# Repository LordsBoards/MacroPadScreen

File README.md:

# A macropad + numpad to keep close by on your desk.
Uses the https://www.adafruit.com/product/2158 many-segment display for cyberpunk aesthetics

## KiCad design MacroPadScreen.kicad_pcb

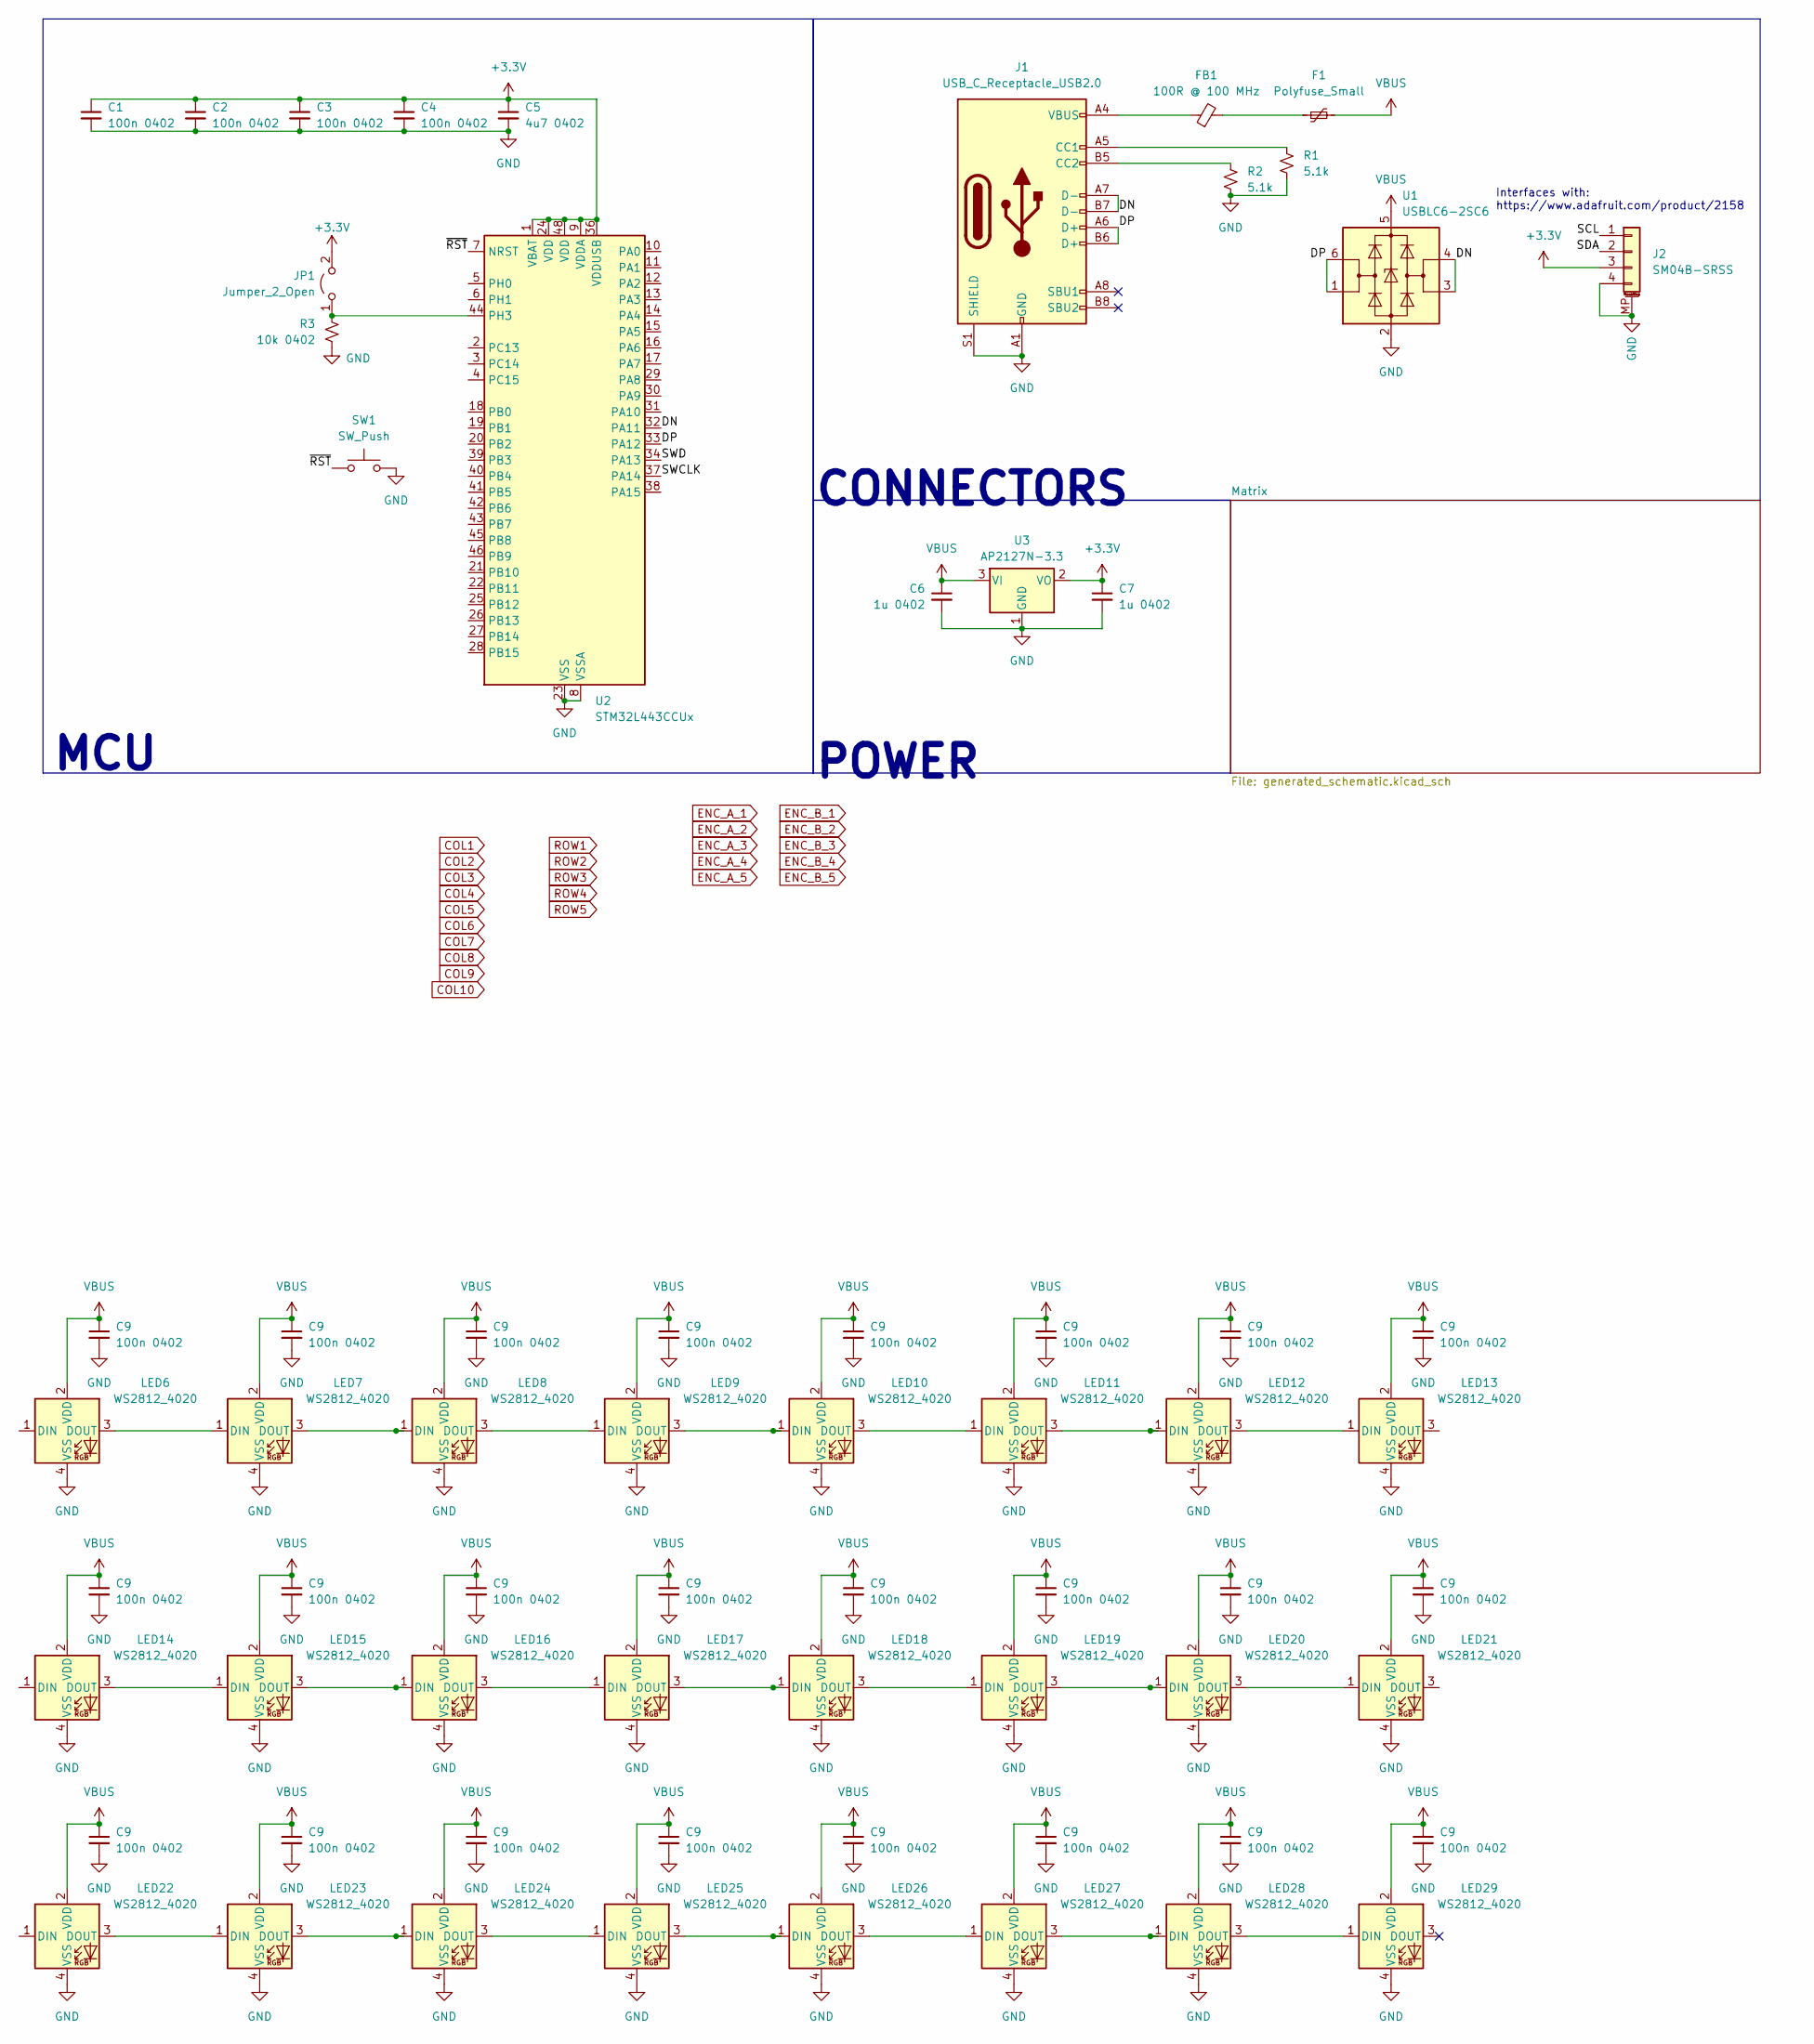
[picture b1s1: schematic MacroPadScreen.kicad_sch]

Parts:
C1, C2, C3, C4, C9: 100n 0402; C_0402_1005Metric
C5: 4u7 0402; C_0402_1005Metric
C6, C7: 1u 0402; C_0402_1005Metric
F1: Polyfuse_Small
FB1: 100R @ 100 MHz
J1: USB_C_Receptacle_USB2.0; USB_C_Receptacle_HRO_TYPE-C-31-M-12
J2: SM04B-SRSS; JST_SH_SM04B-SRSS-TB_1x04-1MP_P1.00mm_Horizontal; Manufacturer Part Number SM04B-SRSS-TB; LCSC Part Number C160404
JP1: Jumper_2_Open; PinHeader_1x02_P1.27mm_Vertical
LED6, LED7, LED8, LED9, LED10, LED11, LED12, LED13, LED14, LED15, LED16, LED17, LED18, LED19, LED20, LED21, LED22, LED23, LED24, LED25, LED26, LED27, LED28, LED29: WS2812_4020; LED_WS2812_4020
R1, R2: 5.1k; R_0402_1005Metric
R3: 10k 0402; R_0402_1005Metric; LCSC C60490
SW1: SW_Push; SW_Push_1P1T_XKB_TS-1187A
U1: USBLC6-2SC6; SOT-23-6
U2: STM32L443CCUx; QFN-48-1EP_7x7mm_P0.5mm_EP5.6x5.6mm
U3: AP2127N-3.3; SOT-23

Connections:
+3.3V: C1.1, C2.1, C3.1, C4.1, C5.1, C7.1, J2.3, JP1.2 (B), U2.1 (VBAT), U2.9 (VDDA), U2.24 (VDD), U2.36 (VDDUSB), U2.48 (VDD), U3.2 (VO); also elsewhere on the board
/DN: J1.A7 (D-), J1.B7 (D-), U1.3 (I/O2), U1.4 (I/O2), U2.32 (PA11)
/DP: J1.A6 (D+), J1.B6 (D+), U1.1 (I/O1), U1.6 (I/O1), U2.33 (PA12)
/SCL: J2.1
/SDA: J2.2
/SWCLK: U2.37 (PA14)
/SWD: U2.34 (PA13)
/~RST: SW1.1, U2.7 (NRST)
GND: C1.2, C2.2, C3.2, C4.2, C5.2, C6.2, C7.2, C9.2, J1.A1 (GND), J1.A12 (GND), J1.B1 (GND), J1.B12 (GND), J1.S1 (SHIELD), J2.4, J2.MP (MountPin), LED6.4 (VSS), LED7.4 (VSS), LED8.4 (VSS), LED9.4 (VSS), LED10.4 (VSS), LED11.4 (VSS), LED12.4 (VSS), LED13.4 (VSS), LED14.4 (VSS), LED15.4 (VSS), LED16.4 (VSS), LED17.4 (VSS), LED18.4 (VSS), LED19.4 (VSS), LED20.4 (VSS), LED21.4 (VSS), LED22.4 (VSS), LED23.4 (VSS), LED24.4 (VSS), LED25.4 (VSS), LED26.4 (VSS), LED27.4 (VSS), LED28.4 (VSS), LED29.4 (VSS), R1.2, R2.2, R3.2, SW1.2, U1.2 (GND), U2.8 (VSSA), U2.23 (VSS), U2.35 (VSS), U2.47 (VSS), U2.49 (VSS), U3.1 (GND); also elsewhere on the board
unnamed: F1.1, FB1.2
unnamed: FB1.1, J1.A4 (VBUS), J1.A9 (VBUS), J1.B4 (VBUS), J1.B9 (VBUS)
unnamed: J1.A5 (CC1), R1.1
unnamed: J1.B5 (CC2), R2.1
unnamed: JP1.1 (A), R3.1, U2.44 (PH3)
unnamed: LED6.3 (DOUT), LED7.1 (DIN)
unnamed: LED7.3 (DOUT), LED8.1 (DIN)
unnamed: LED8.3 (DOUT), LED9.1 (DIN)
unnamed: LED9.3 (DOUT), LED10.1 (DIN)
unnamed: LED10.3 (DOUT), LED11.1 (DIN)
unnamed: LED11.3 (DOUT), LED12.1 (DIN)
unnamed: LED12.3 (DOUT), LED13.1 (DIN)
unnamed: LED14.3 (DOUT), LED15.1 (DIN)
unnamed: LED15.3 (DOUT), LED16.1 (DIN)
unnamed: LED16.3 (DOUT), LED17.1 (DIN)
unnamed: LED17.3 (DOUT), LED18.1 (DIN)
unnamed: LED18.3 (DOUT), LED19.1 (DIN)
unnamed: LED19.3 (DOUT), LED20.1 (DIN)
unnamed: LED20.3 (DOUT), LED21.1 (DIN)
unnamed: LED22.3 (DOUT), LED23.1 (DIN)
unnamed: LED23.3 (DOUT), LED24.1 (DIN)
unnamed: LED24.3 (DOUT), LED25.1 (DIN)
unnamed: LED25.3 (DOUT), LED26.1 (DIN)
unnamed: LED26.3 (DOUT), LED27.1 (DIN)
unnamed: LED27.3 (DOUT), LED28.1 (DIN)
unnamed: LED28.3 (DOUT), LED29.1 (DIN)
VBUS: C6.1, C9.1, LED6.2 (VDD), LED7.2 (VDD), LED8.2 (VDD), LED9.2 (VDD), LED10.2 (VDD), LED11.2 (VDD), LED12.2 (VDD), LED13.2 (VDD), LED14.2 (VDD), LED15.2 (VDD), LED16.2 (VDD), LED17.2 (VDD), LED18.2 (VDD), LED19.2 (VDD), LED20.2 (VDD), LED21.2 (VDD), LED22.2 (VDD), LED23.2 (VDD), LED24.2 (VDD), LED25.2 (VDD), LED26.2 (VDD), LED27.2 (VDD), LED28.2 (VDD), LED29.2 (VDD), U1.5 (VBUS), U3.3 (VI); also elsewhere on the board

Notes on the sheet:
POWER
Interfaces with: https://www.adafruit.com/product/2158
MCU
CONNECTORS

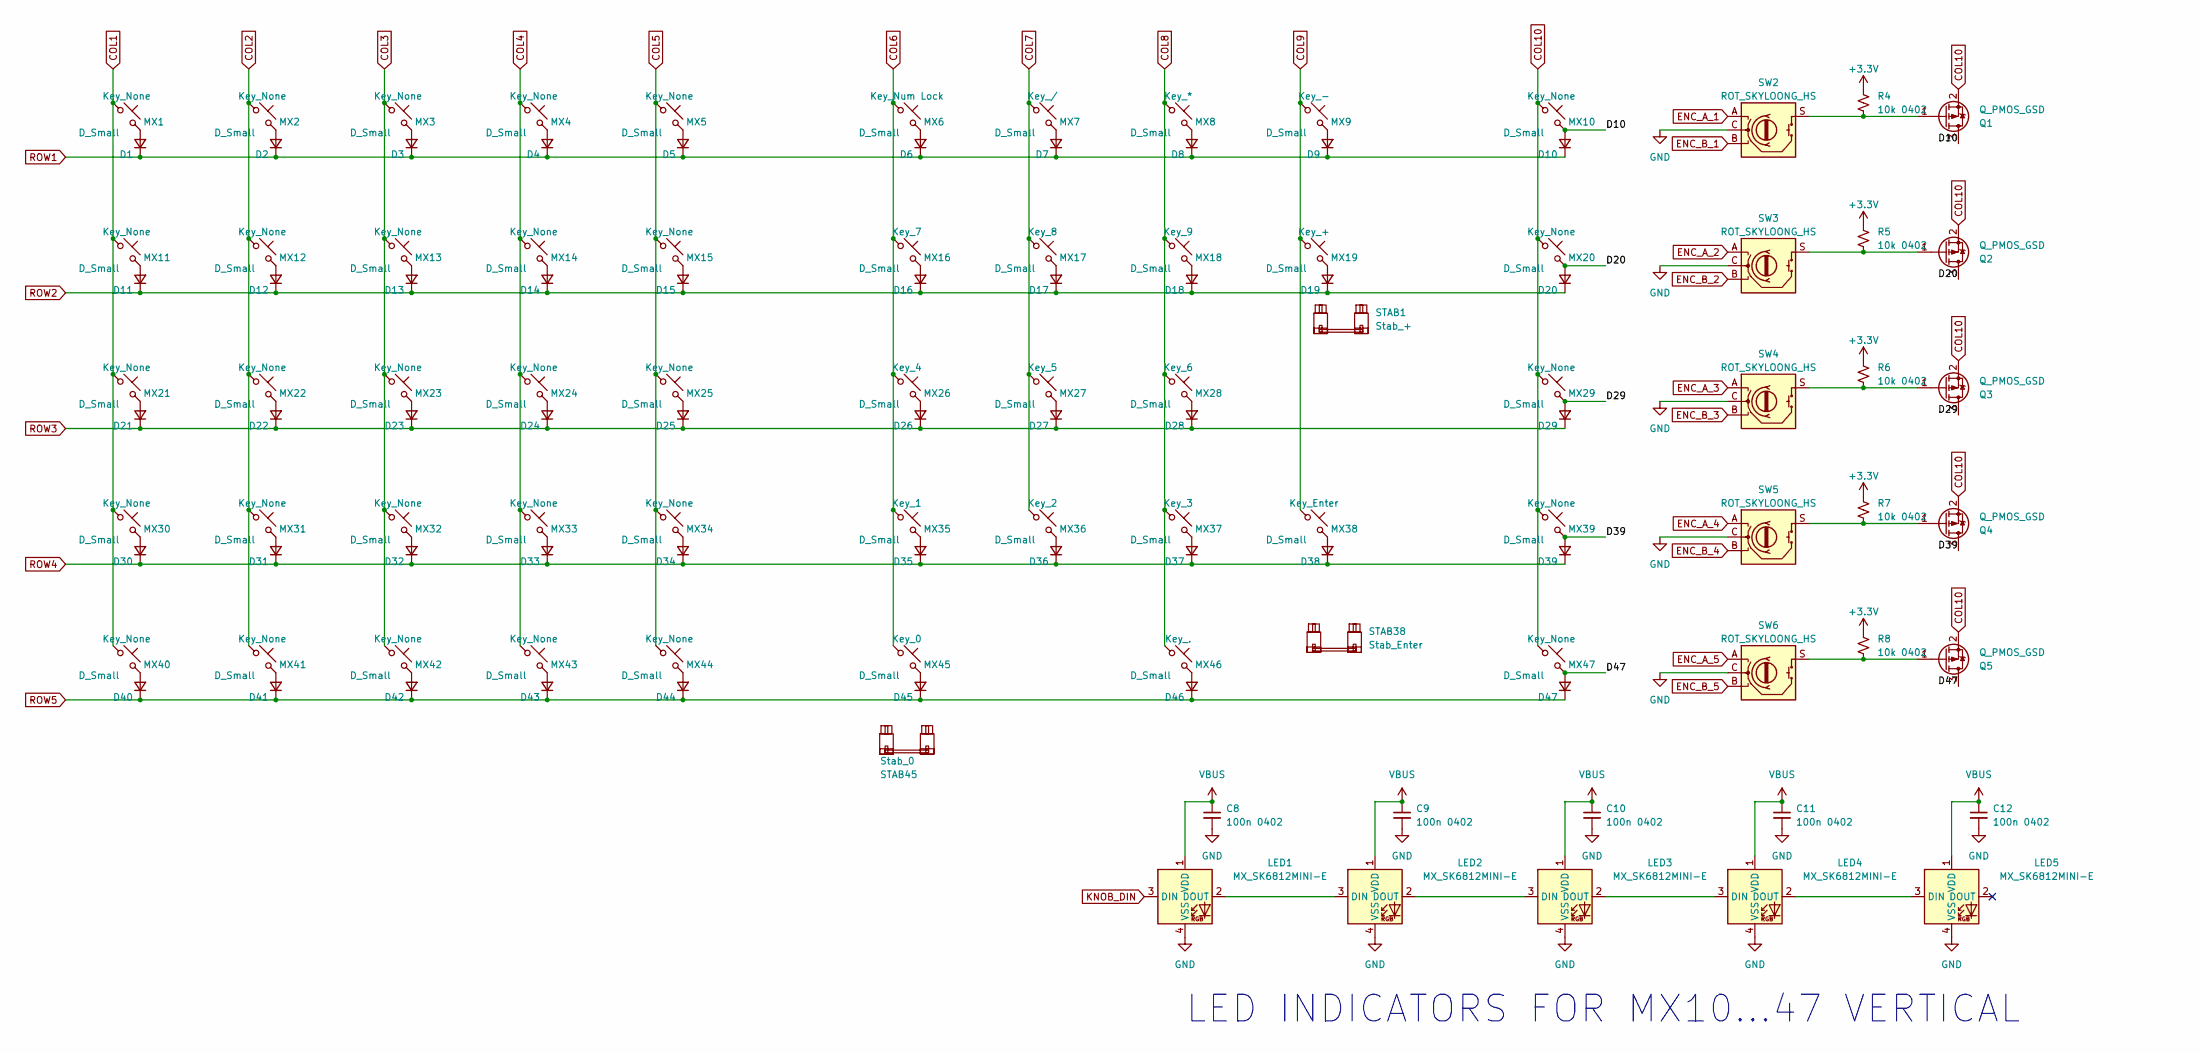
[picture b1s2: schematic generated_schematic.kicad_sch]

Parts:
C8, C9, C10, C11, C12: 100n 0402; C_0402_1005Metric
D1, D2, D3, D4, D5, D6, D7, D8, D9, D10, D11, D12, D13, D14, D15, D16, D17, D18, D19, D20, D21, D22, D23, D24, D25, D26, D27, D28, D29, D30, D31, D32, D33, D34, D35, D36, D37, D38, D39, D40, D41, D42, D43, D44, D45, D46, D47: D_Small; D_SOD-123
LED1, LED2, LED3, LED4, LED5: MX_SK6812MINI-E; LED_MX_6028R
MX1, MX2, MX3, MX4, MX5, MX10, MX11, MX12, MX13, MX14, MX15, MX20, MX21, MX22, MX23, MX24, MX25, MX29, MX30, MX31, MX32, MX33, MX34, MX39, MX40, MX41, MX42, MX43, MX44, MX47: Key_None; SW_MX_HS_S_1u
MX6: Key_Num Lock; SW_MX_HS_S_1u
MX7: Key_/; SW_MX_HS_S_1u
MX8: Key_*; SW_MX_HS_S_1u
MX9: Key_-; SW_MX_HS_S_1u
MX16: Key_7; SW_MX_HS_S_1u
MX17: Key_8; SW_MX_HS_S_1u
MX18: Key_9; SW_MX_HS_S_1u
MX19: Key_+; SW_MX_HS_S_1u
MX26: Key_4; SW_MX_HS_S_1u
MX27: Key_5; SW_MX_HS_S_1u
MX28: Key_6; SW_MX_HS_S_1u
MX35: Key_1; SW_MX_HS_S_1u
MX36: Key_2; SW_MX_HS_S_1u
MX37: Key_3; SW_MX_HS_S_1u
MX38: Key_Enter; SW_MX_HS_S_1u
MX45: Key_0; SW_MX_HS_S_1u
MX46: Key_.; SW_MX_HS_S_1u
Q1, Q2, Q3, Q4, Q5: Q_PMOS_GSD; SOT-23
R4, R5, R6, R7, R8: 10k 0402; R_0402_1005Metric
STAB1: Stab_+; STAB_MX_P_2u
STAB38: Stab_Enter; STAB_MX_P_2u
STAB45: Stab_0; STAB_MX_P_2u
SW2, SW3, SW4, SW5, SW6: ROT_SKYLOONG_HS; ROT_SKYLOONG_HS-Switch

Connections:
+3.3V: R4.1, R5.1, R6.1, R7.1, R8.1; also elsewhere on the board
/Matrix/D10: D10.2 (A), MX10.2, Q1.3 (D)
/Matrix/D20: D20.2 (A), MX20.2, Q2.3 (D)
/Matrix/D29: D29.2 (A), MX29.2, Q3.3 (D)
/Matrix/D39: D39.2 (A), MX39.2, Q4.3 (D)
/Matrix/D47: D47.2 (A), MX47.2, Q5.3 (D)
COL1: MX1.1, MX11.1, MX21.1, MX30.1, MX40.1
COL2: MX2.1, MX12.1, MX22.1, MX31.1, MX41.1
COL3: MX3.1, MX13.1, MX23.1, MX32.1, MX42.1
COL4: MX4.1, MX14.1, MX24.1, MX33.1, MX43.1
COL5: MX5.1, MX15.1, MX25.1, MX34.1, MX44.1
COL6: MX6.1, MX16.1, MX26.1, MX35.1, MX45.1
COL7: MX7.1, MX17.1, MX27.1, MX36.1
COL8: MX8.1, MX18.1, MX28.1, MX37.1, MX46.1
COL9: MX9.1, MX19.1, MX38.1
COL10: MX10.1, MX20.1, MX29.1, MX39.1, MX47.1, Q1.2 (S), Q2.2 (S), Q3.2 (S), Q4.2 (S), Q5.2 (S)
ENC_A_1: SW2.A
ENC_A_2: SW3.A
ENC_A_3: SW4.A
ENC_A_4: SW5.A
ENC_A_5: SW6.A
ENC_B_1: SW2.B
ENC_B_2: SW3.B
ENC_B_3: SW4.B
ENC_B_4: SW5.B
ENC_B_5: SW6.B
GND: C8.2, C9.2, C10.2, C11.2, C12.2, LED1.4 (VSS), LED2.4 (VSS), LED3.4 (VSS), LED4.4 (VSS), LED5.4 (VSS), SW2.C, SW3.C, SW4.C, SW5.C, SW6.C; also elsewhere on the board
KNOB_DIN: LED1.3 (DIN)
unnamed: D1.2 (A), MX1.2
unnamed: D2.2 (A), MX2.2
unnamed: D3.2 (A), MX3.2
unnamed: D4.2 (A), MX4.2
unnamed: D5.2 (A), MX5.2
unnamed: D6.2 (A), MX6.2
unnamed: D7.2 (A), MX7.2
unnamed: D8.2 (A), MX8.2
unnamed: D9.2 (A), MX9.2
unnamed: D11.2 (A), MX11.2
unnamed: D12.2 (A), MX12.2
unnamed: D13.2 (A), MX13.2
unnamed: D14.2 (A), MX14.2
unnamed: D15.2 (A), MX15.2
unnamed: D16.2 (A), MX16.2
unnamed: D17.2 (A), MX17.2
unnamed: D18.2 (A), MX18.2
unnamed: D19.2 (A), MX19.2
unnamed: D21.2 (A), MX21.2
unnamed: D22.2 (A), MX22.2
unnamed: D23.2 (A), MX23.2
unnamed: D24.2 (A), MX24.2
unnamed: D25.2 (A), MX25.2
unnamed: D26.2 (A), MX26.2
unnamed: D27.2 (A), MX27.2
unnamed: D28.2 (A), MX28.2
unnamed: D30.2 (A), MX30.2
unnamed: D31.2 (A), MX31.2
unnamed: D32.2 (A), MX32.2
unnamed: D33.2 (A), MX33.2
unnamed: D34.2 (A), MX34.2
unnamed: D35.2 (A), MX35.2
unnamed: D36.2 (A), MX36.2
unnamed: D37.2 (A), MX37.2
unnamed: D38.2 (A), MX38.2
unnamed: D40.2 (A), MX40.2
unnamed: D41.2 (A), MX41.2
unnamed: D42.2 (A), MX42.2
unnamed: D43.2 (A), MX43.2
unnamed: D44.2 (A), MX44.2
unnamed: D45.2 (A), MX45.2
unnamed: D46.2 (A), MX46.2
unnamed: LED1.2 (DOUT), LED2.3 (DIN)
unnamed: LED2.2 (DOUT), LED3.3 (DIN)
unnamed: LED3.2 (DOUT), LED4.3 (DIN)
unnamed: LED4.2 (DOUT), LED5.3 (DIN)
unnamed: Q1.1 (G), R4.2, SW2.S
unnamed: Q2.1 (G), R5.2, SW3.S
unnamed: Q3.1 (G), R6.2, SW4.S
unnamed: Q4.1 (G), R7.2, SW5.S
unnamed: Q5.1 (G), R8.2, SW6.S
ROW1: D1.1 (K), D2.1 (K), D3.1 (K), D4.1 (K), D5.1 (K), D6.1 (K), D7.1 (K), D8.1 (K), D9.1 (K), D10.1 (K)
ROW2: D11.1 (K), D12.1 (K), D13.1 (K), D14.1 (K), D15.1 (K), D16.1 (K), D17.1 (K), D18.1 (K), D19.1 (K), D20.1 (K)
ROW3: D21.1 (K), D22.1 (K), D23.1 (K), D24.1 (K), D25.1 (K), D26.1 (K), D27.1 (K), D28.1 (K), D29.1 (K)
ROW4: D30.1 (K), D31.1 (K), D32.1 (K), D33.1 (K), D34.1 (K), D35.1 (K), D36.1 (K), D37.1 (K), D38.1 (K), D39.1 (K)
ROW5: D40.1 (K), D41.1 (K), D42.1 (K), D43.1 (K), D44.1 (K), D45.1 (K), D46.1 (K), D47.1 (K)
VBUS: C8.1, C9.1, C10.1, C11.1, C12.1, LED1.1 (VDD), LED2.1 (VDD), LED3.1 (VDD), LED4.1 (VDD), LED5.1 (VDD); also elsewhere on the board

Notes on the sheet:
LED INDICATORS FOR MX10...47 VERTICAL

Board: 4 copper layers, 187 parts (179 on the bottom side), 102 nets, no tracks yet.

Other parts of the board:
C13, C14, C15, C16, C17, C18, C19, C20, C21, C22, C23, C24, C25, C26, C27, C28, C29, C30, C31, C32, C33, C34, C35, C36: 100n 0402; C_0402_1005Metric

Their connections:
GND: C13.2, C14.2, C15.2, C16.2, C17.2, C18.2, C19.2, C20.2, C21.2, C22.2, C23.2, C24.2, C25.2, C26.2, C27.2, C28.2, C29.2, C30.2, C31.2, C32.2, C33.2, C34.2, C35.2, C36.2; also elsewhere on the board
VBUS: C13.1, C14.1, C15.1, C16.1, C17.1, C18.1, C19.1, C20.1, C21.1, C22.1, C23.1, C24.1, C25.1, C26.1, C27.1, C28.1, C29.1, C30.1, C31.1, C32.1, C33.1, C34.1, C35.1, C36.1; also elsewhere on the board
